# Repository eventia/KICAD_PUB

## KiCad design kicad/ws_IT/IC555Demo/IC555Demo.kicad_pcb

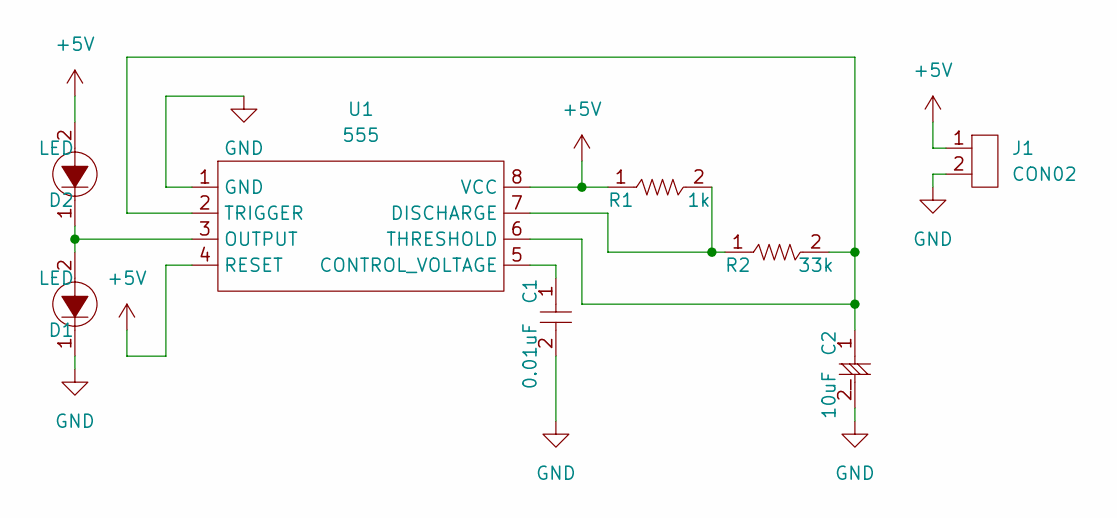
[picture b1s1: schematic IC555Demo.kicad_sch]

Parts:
C1: 0.01uF; Cap1
C2: 10uF; Cap2
D1, D2: LED; LED_D5.0mm
J1: CON02; CON_02
R1: 1k; Resistor
R2: 33k; Resistor
U1: 555; 555_DIP

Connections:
+5V: D2.2, J1.1, R1.1, U1.4 (RESET), U1.8 (VCC)
GND: C1.2, C2.2, D1.1, J1.2, U1.1 (GND)
unnamed: C1.1, U1.5 (CONTROL_VOLTAGE)
unnamed: C2.1, R2.2, U1.2 (TRIGGER), U1.6 (THRESHOLD)
unnamed: D1.2, D2.1, U1.3 (OUTPUT)
unnamed: R1.2, R2.1, U1.7 (DISCHARGE)

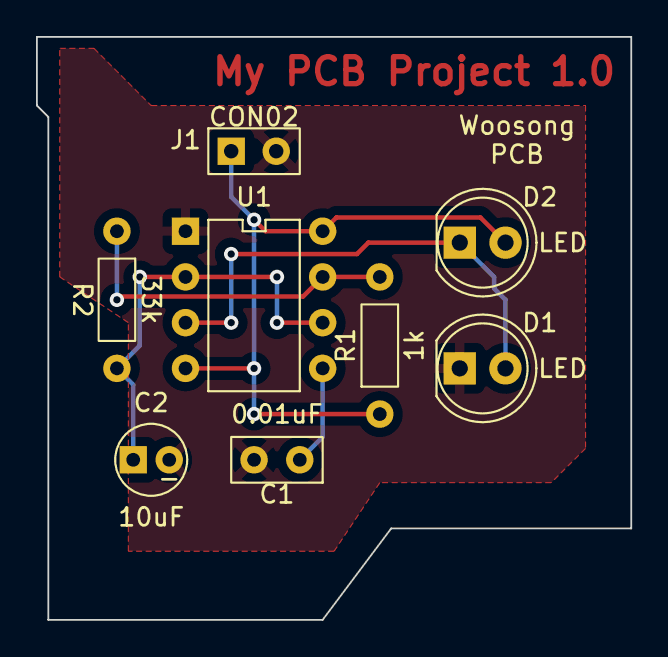
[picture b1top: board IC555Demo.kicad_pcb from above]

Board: 2 copper layers, 33.0 x 32.4 mm, 8 parts (0 on the bottom side), 6 nets.

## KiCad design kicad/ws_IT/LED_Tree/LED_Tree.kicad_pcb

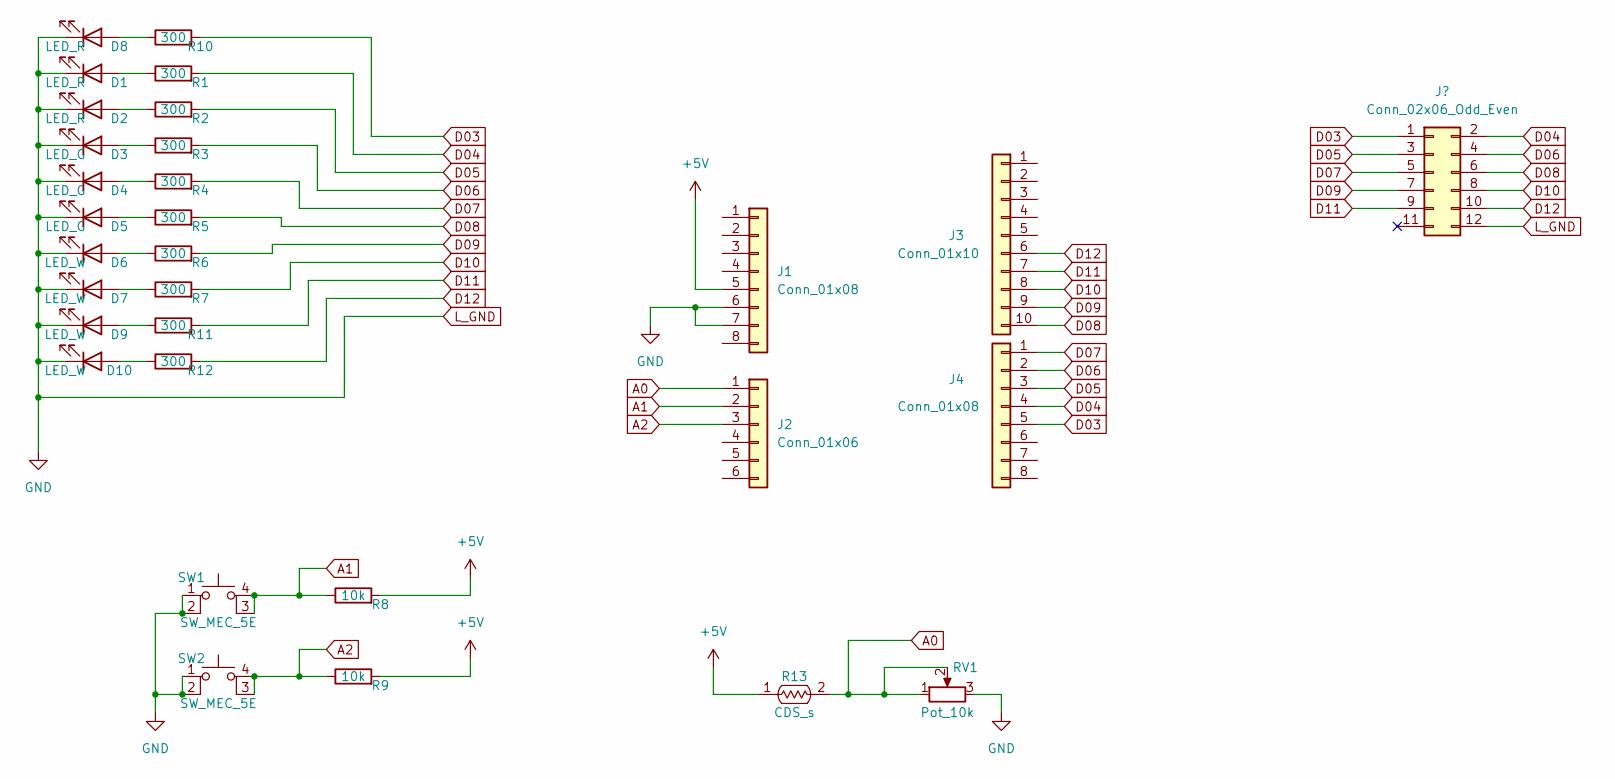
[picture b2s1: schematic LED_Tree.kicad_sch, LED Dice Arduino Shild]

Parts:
D1, D2, D8: LED_R; LED_0603_1608Metric_Pad1.05x0.95mm_HandSolder
D3, D4, D5: LED_G; LED_0603_1608Metric_Pad1.05x0.95mm_HandSolder
D6, D7, D9, D10: LED_W; LED_0603_1608Metric_Pad1.05x0.95mm_HandSolder
J1, J4: Conn_01x08; PinHeader_1x08_P2.54mm_Vertical
J2: Conn_01x06; PinHeader_1x06_P2.54mm_Vertical
J3: Conn_01x10; PinHeader_1x10_P2.54mm_Vertical
R1, R2, R3, R4, R5, R6, R7, R10, R11, R12: 300; R_0603_1608Metric_Pad0.98x0.95mm_HandSolder
R8, R9: 10k; R_0603_1608Metric_Pad0.98x0.95mm_HandSolder
R13: CDS_s
RV1: Pot_10k; R_POT_10k_VZ067TL7-10K
SW1, SW2: SW_MEC_5E; Tact_Switch_ITS-1105

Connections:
+5V: J1.5, R8.2, R9.2, R13.1
A0: J2.1, R13.2, RV1.1, RV1.2
A1: J2.2, R8.1, SW1.3 (K), SW1.4 (A)
A2: J2.3, R9.1, SW2.3 (K), SW2.4 (A)
D03: J4.5, R10.2
D04: J4.4, R1.2
D05: J4.3, R2.2
D06: J4.2, R3.2
D07: J4.1, R4.2
D08: J3.10, R5.2
D09: J3.9, R6.2
D10: J3.8, R7.2
D11: J3.7, R11.2
D12: J3.6, R12.2
GND: D1.1 (K), D2.1 (K), D3.1 (K), D4.1 (K), D5.1 (K), D6.1 (K), D7.1 (K), D8.1 (K), D9.1 (K), D10.1 (K), J1.6, J1.7, RV1.3, SW1.1, SW1.2, SW2.1, SW2.2
unnamed: D1.2 (A), R1.1
unnamed: D2.2 (A), R2.1
unnamed: D3.2 (A), R3.1
unnamed: D4.2 (A), R4.1
unnamed: D5.2 (A), R5.1
unnamed: D6.2 (A), R6.1
unnamed: D7.2 (A), R7.1
unnamed: D8.2 (A), R10.1
unnamed: D9.2 (A), R11.1
unnamed: D10.2 (A), R12.1

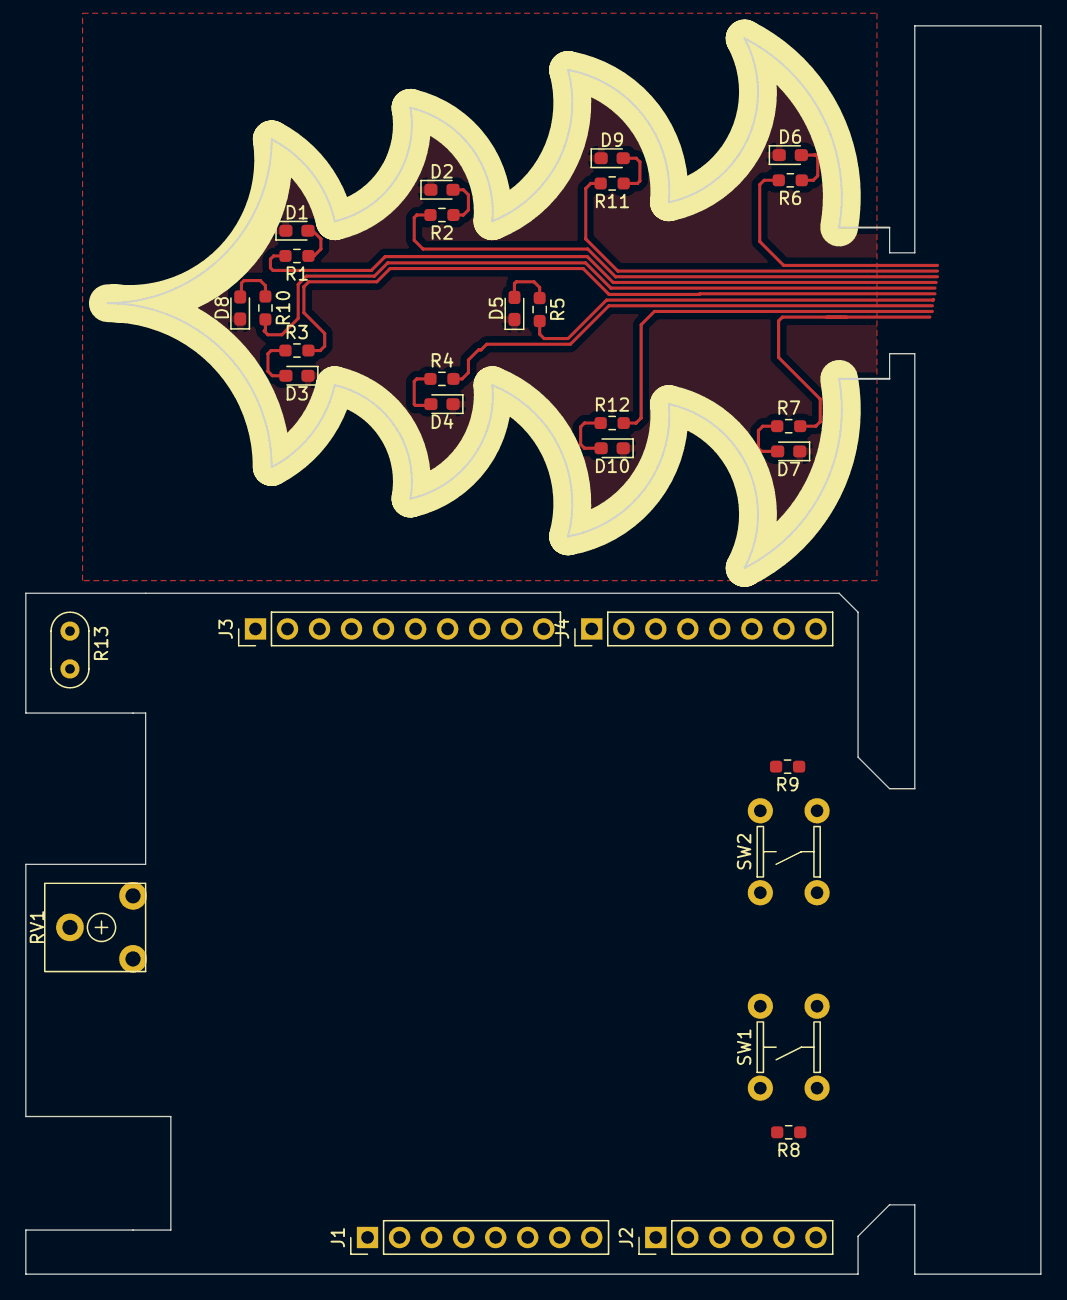
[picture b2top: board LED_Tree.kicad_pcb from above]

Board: 2 copper layers, 80.5 x 99.0 mm, 30 parts (0 on the bottom side), 25 nets.

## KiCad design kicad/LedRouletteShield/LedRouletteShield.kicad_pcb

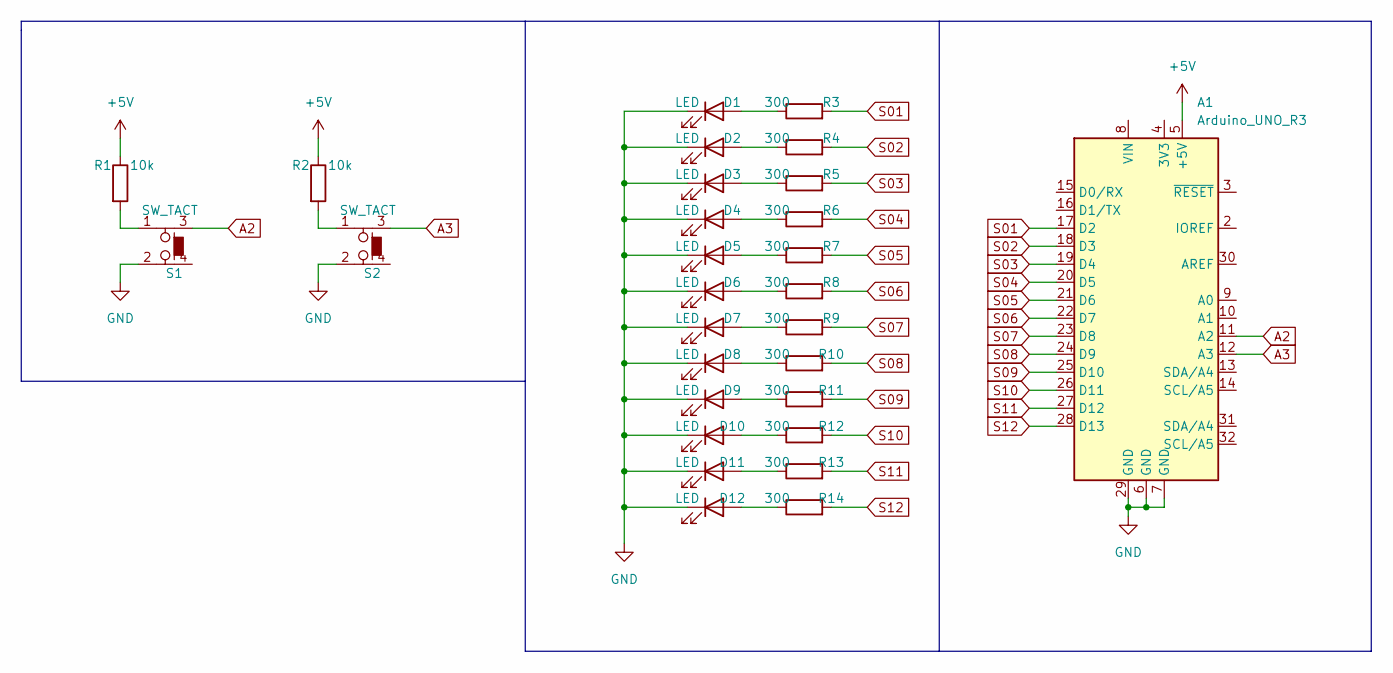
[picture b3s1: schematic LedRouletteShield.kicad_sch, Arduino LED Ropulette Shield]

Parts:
A1: Arduino_UNO_R3
D1, D2, D3, D4, D5, D6, D7, D8, D9, D10, D11, D12: LED; LED_D5.0mm
R1, R2: 10k; R_Axial_DIN0207_L6.3mm_D2.5mm_P7.62mm_Horizontal
R3, R4, R5, R6, R7, R8, R9, R10, R11, R12, R13, R14: 300; R_Axial_DIN0207_L6.3mm_D2.5mm_P7.62mm_Horizontal
S1, S2: SW_TACT; Tact_Switch

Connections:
+5V: A1.5 (+5V), R1.1, R2.1
A2: A1.11 (A2), S1.3
A3: A1.12 (A3), S2.3
GND: A1.6 (GND), A1.7 (GND), A1.29 (GND), D1.1 (K), D2.1 (K), D3.1 (K), D4.1 (K), D5.1 (K), D6.1 (K), D7.1 (K), D8.1 (K), D9.1 (K), D10.1 (K), D11.1 (K), D12.1 (K), S1.2, S2.2
unnamed: D1.2 (A), R3.1
unnamed: D2.2 (A), R4.1
unnamed: D3.2 (A), R5.1
unnamed: D4.2 (A), R6.1
unnamed: D5.2 (A), R7.1
unnamed: D6.2 (A), R8.1
unnamed: D7.2 (A), R9.1
unnamed: D8.2 (A), R10.1
unnamed: D9.2 (A), R11.1
unnamed: D10.2 (A), R12.1
unnamed: D11.2 (A), R13.1
unnamed: D12.2 (A), R14.1
unnamed: R1.2, S1.1
unnamed: R2.2, S2.1
S01: A1.17 (D2), R3.2
S02: A1.18 (D3), R4.2
S03: A1.19 (D4), R5.2
S04: A1.20 (D5), R6.2
S05: A1.21 (D6), R7.2
S06: A1.22 (D7), R8.2
S07: A1.23 (D8), R9.2
S08: A1.24 (D9), R10.2
S09: A1.25 (D10), R11.2
S10: A1.26 (D11), R12.2
S11: A1.27 (D12), R13.2
S12: A1.28 (D13), R14.2

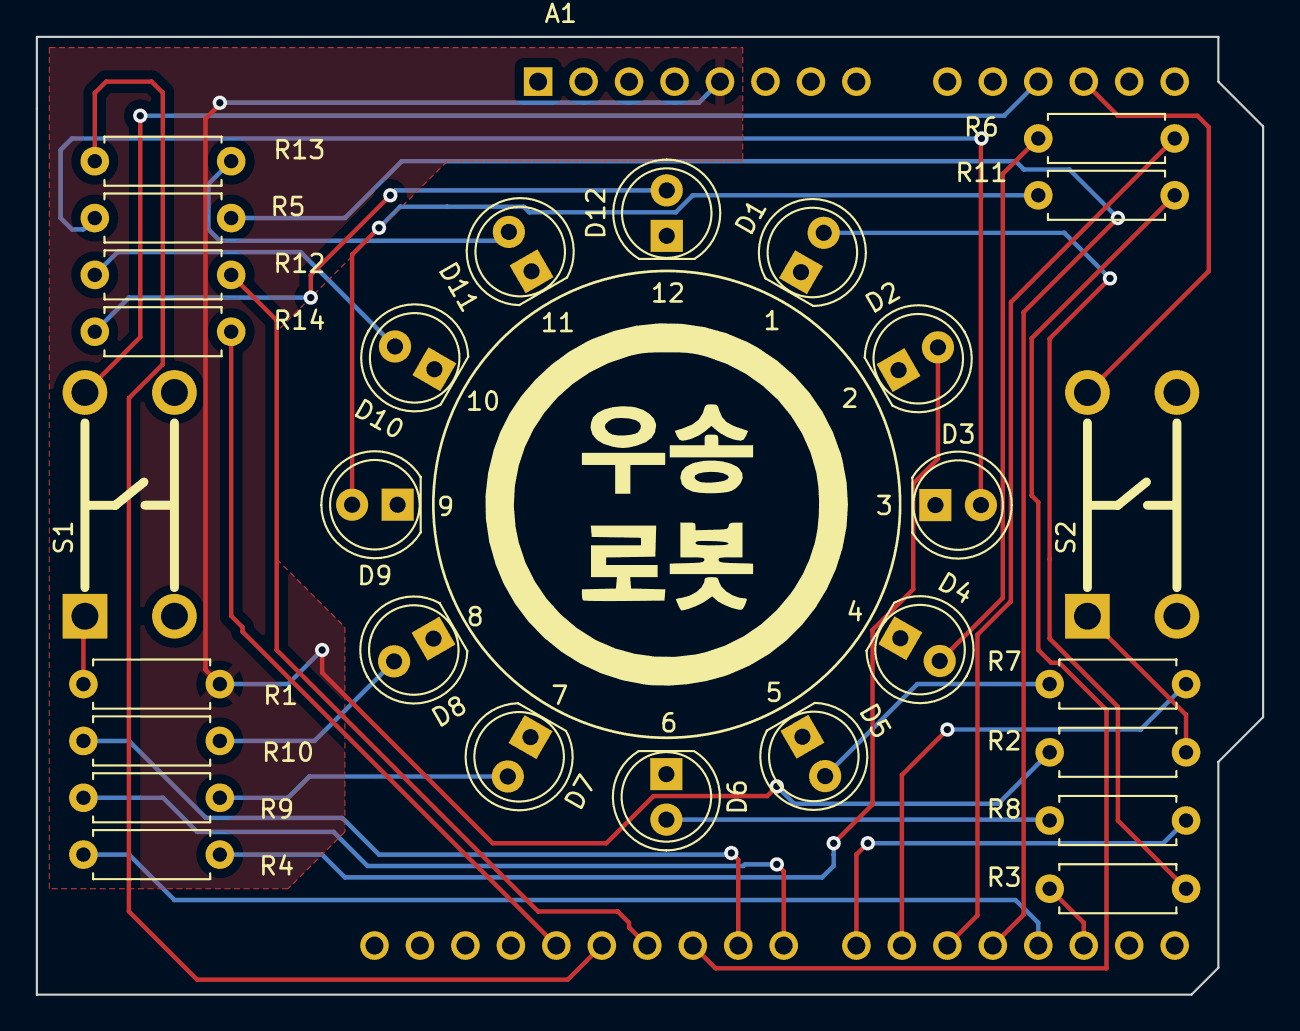
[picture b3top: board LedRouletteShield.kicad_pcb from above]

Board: 2 copper layers, 68.5 x 53.5 mm, 29 parts (0 on the bottom side), 30 nets.

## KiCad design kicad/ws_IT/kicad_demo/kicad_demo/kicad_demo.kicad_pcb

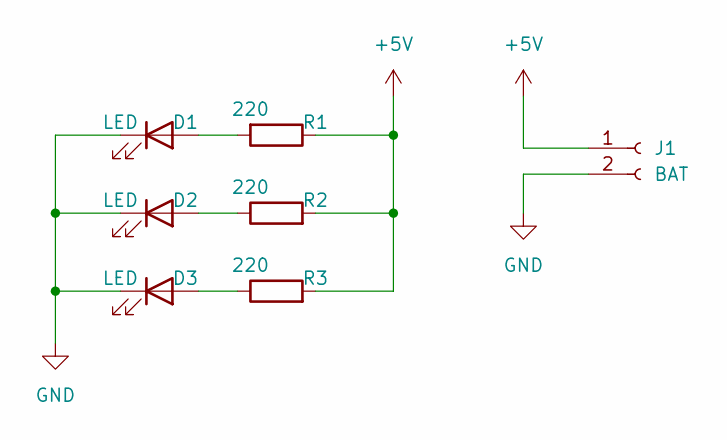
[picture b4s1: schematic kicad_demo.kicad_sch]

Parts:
D1, D2, D3: LED; LED_D5.0mm
J1: BAT; Molex_SPOX_5267-02A_1x02_P2.50mm_Vertical
R1, R2, R3: 220; R_Axial_DIN0207_L6.3mm_D2.5mm_P7.62mm_Horizontal

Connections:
+5V: J1.1, R1.1, R2.2, R3.2
GND: D1.1 (K), D2.1 (K), D3.1 (K), J1.2
unnamed: D1.2 (A), R1.2
unnamed: D2.2 (A), R2.1
unnamed: D3.2 (A), R3.1

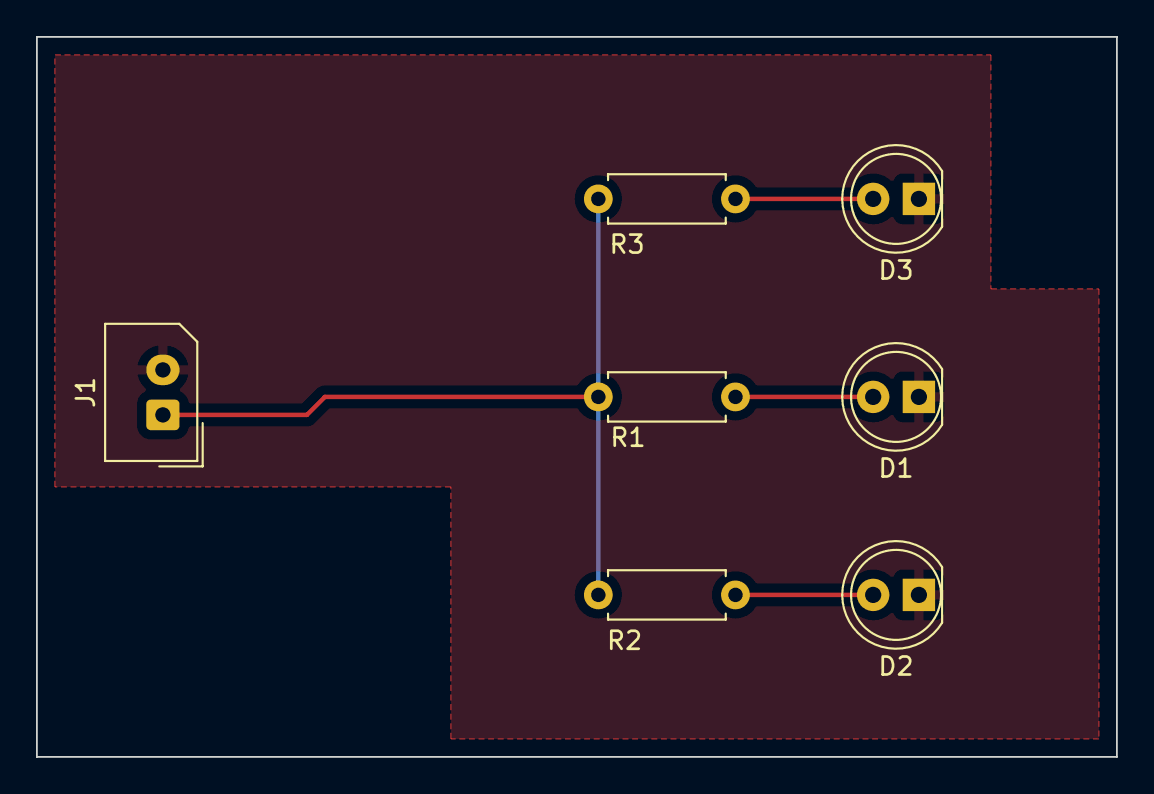
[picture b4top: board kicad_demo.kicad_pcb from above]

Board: 2 copper layers, 60.0 x 40.0 mm, 7 parts (0 on the bottom side), 5 nets.

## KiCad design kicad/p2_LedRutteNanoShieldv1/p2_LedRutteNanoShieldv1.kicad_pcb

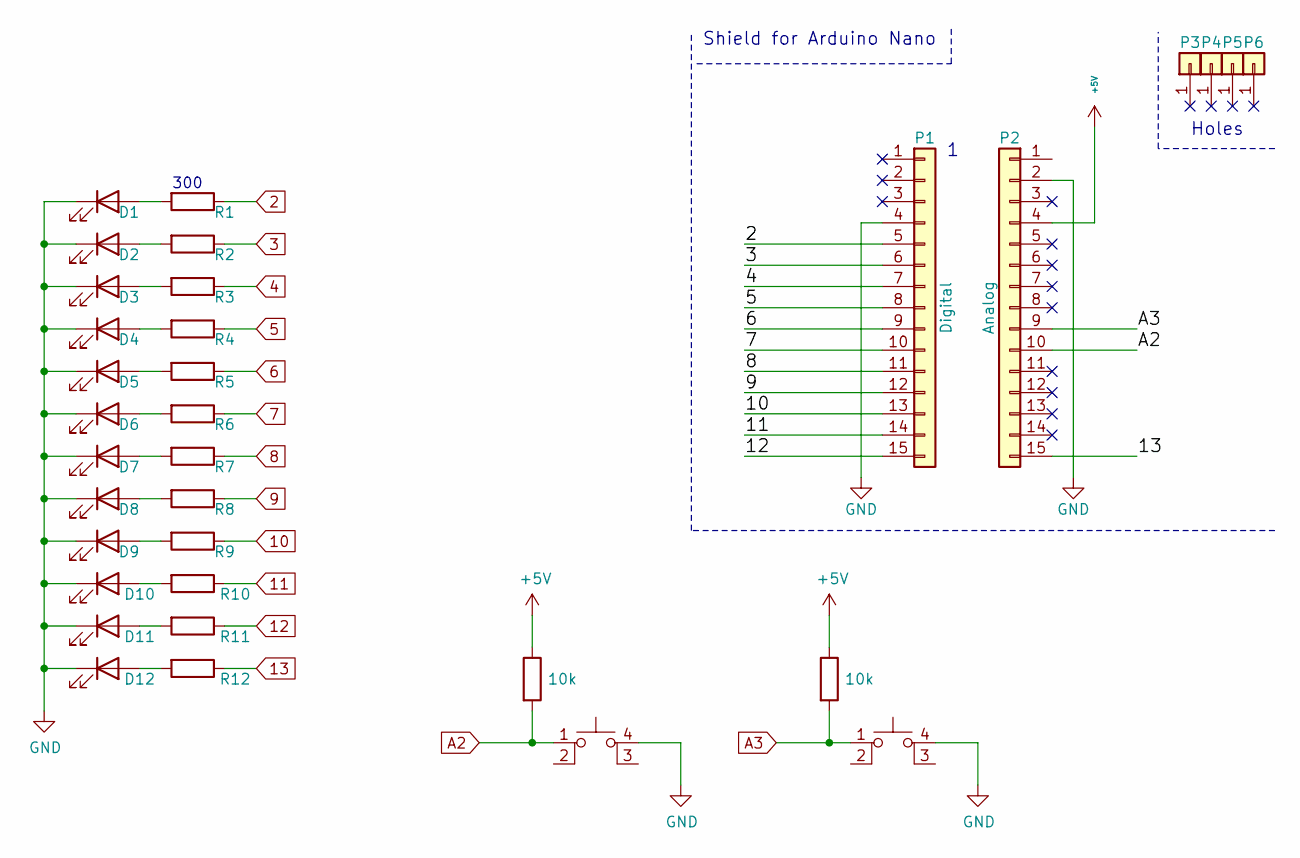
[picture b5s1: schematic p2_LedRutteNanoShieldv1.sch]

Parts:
D1, D2, D3, D4, D5, D6, D7, D8, D9, D10, D11, D12: LED; LED_0805_2012Metric
P1: Digital; Socket_Strip_Arduino_1x15
P2: Analog; Socket_Strip_Arduino_1x15
P3, P4, P5, P6: CONN_01X01; 1pin_Nano
R1, R2, R3, R4, R5, R6, R7, R8, R9, R10, R11, R12: R; R_0603_1608Metric
R13, R14: 10k; R_0603_1608Metric
SW1, SW2: SW_MEC_5E; SW_TH_Tactile_Omron_B3F-10xx

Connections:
2: P1.5, R1.1
3: P1.6, R2.1
4: P1.7, R3.1
5: P1.8, R4.1
6: P1.9, R5.1
7: P1.10, R6.1
8: P1.11, R7.1
9: P1.12, R8.1
10: P1.13, R9.1
11: P1.14, R10.1
12: P1.15, R11.1
13: P2.15, R12.1
+5V: P2.4, R13.1, R14.1
A2: P2.10, R13.2, SW1.1
A3: P2.9, R14.2, SW2.1
GND: D1.1 (K), D2.1 (K), D3.1 (K), D4.1 (K), D5.1 (K), D6.1 (K), D7.1 (K), D8.1 (K), D9.1 (K), D10.1 (K), D11.1 (K), D12.1 (K), P1.4, P2.2, SW1.4 (A), SW2.4 (A)
unnamed: D1.2 (A), R1.2
unnamed: D2.2 (A), R2.2
unnamed: D3.2 (A), R3.2
unnamed: D4.2 (A), R4.2
unnamed: D5.2 (A), R5.2
unnamed: D6.2 (A), R6.2
unnamed: D7.2 (A), R7.2
unnamed: D8.2 (A), R8.2
unnamed: D9.2 (A), R9.2
unnamed: D10.2 (A), R10.2
unnamed: D11.2 (A), R11.2
unnamed: D12.2 (A), R12.2

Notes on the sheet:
Holes
Shield for Arduino Nano
300

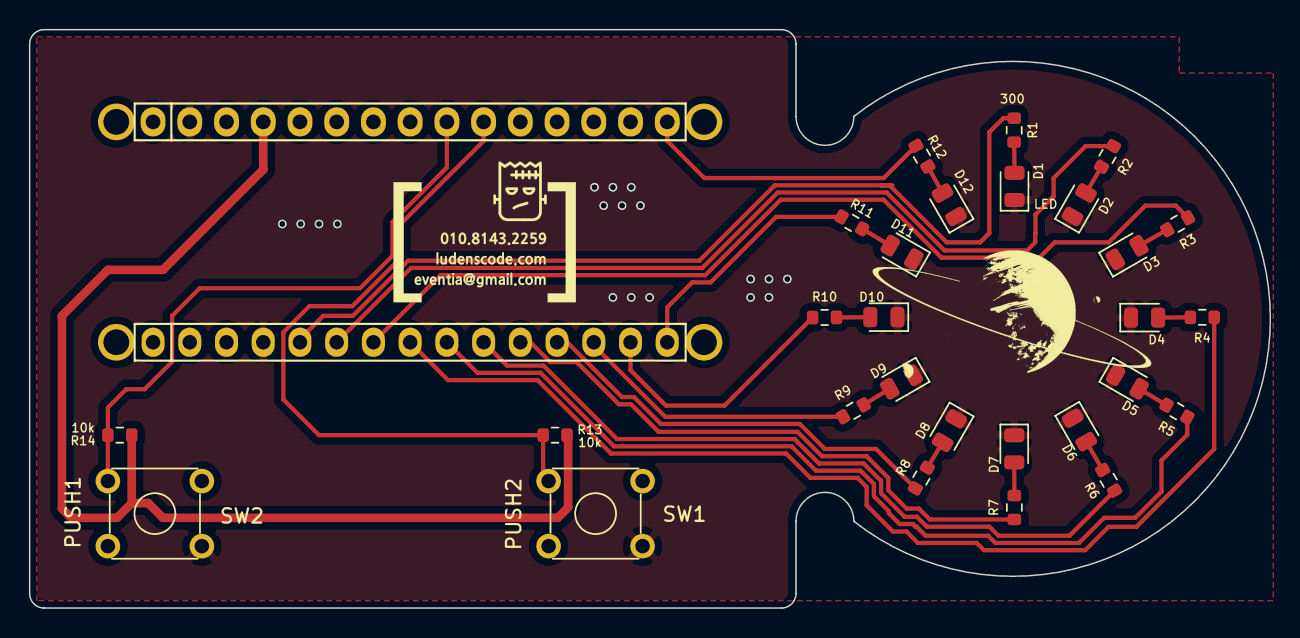
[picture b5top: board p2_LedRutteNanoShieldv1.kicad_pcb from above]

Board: 2 copper layers, 85.8 x 40.0 mm, 34 parts (0 on the bottom side), 28 nets.

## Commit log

2022-09-05 gitignore
2022-09-05 Add JLC2KiCadLib
